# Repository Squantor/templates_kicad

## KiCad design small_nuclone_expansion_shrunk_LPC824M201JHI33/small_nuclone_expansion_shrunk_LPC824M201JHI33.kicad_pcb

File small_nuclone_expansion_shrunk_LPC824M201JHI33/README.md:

# LPC824M201JHI33 nuclone shrunk expansion board 
Template small nuclone expansion board for the [LPC824M201JHI33 nuclone](https://github.com/Squantor/squantorDevelBoards/tree/master/hardware/nuclone_LPC824M201JHI33/README.md).
# HSI (Hardware Software Interface)
This applies to a project that has a embedded software component. Describe what each pin/bus does, what it is connected to, what its function is and some "safe" behaviour when starting up.
## TODO's
Still some things need to be done:
* schematic entry 
* PCB layout
* Review with one night in between
* Produce at [OSHPARK](https://oshpark.com/)
* Assemble
* Test & characterise
* update Readme.md with pictures and BOM
## BOM

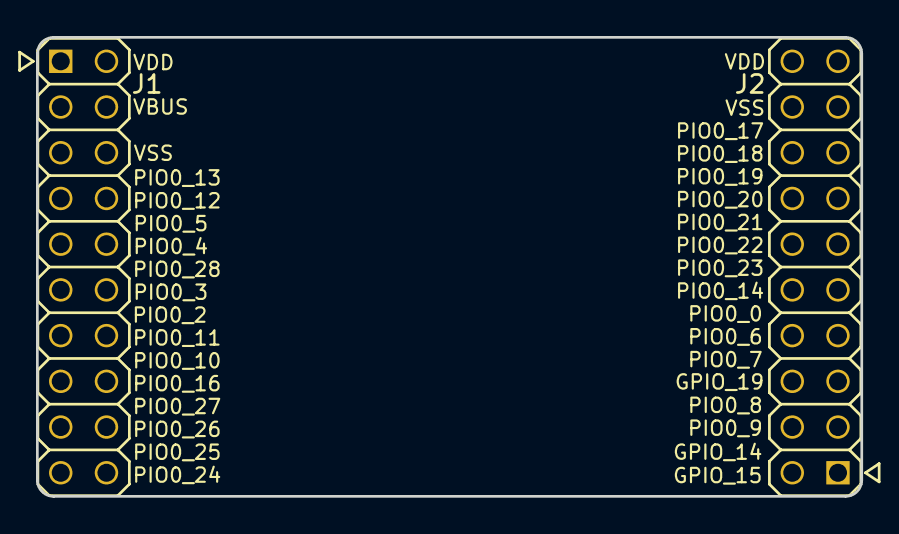
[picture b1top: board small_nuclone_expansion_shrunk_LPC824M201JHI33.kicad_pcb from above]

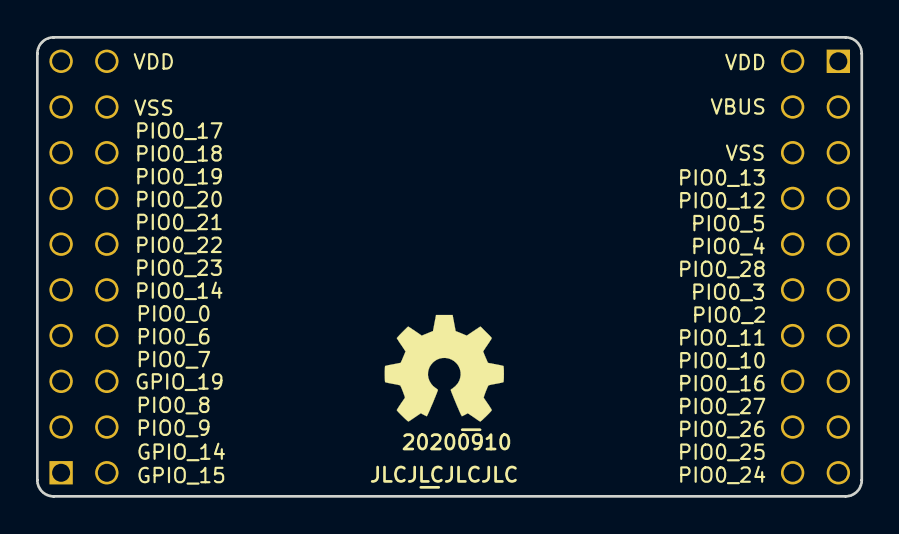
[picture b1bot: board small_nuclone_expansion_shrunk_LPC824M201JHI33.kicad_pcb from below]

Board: 2 copper layers, 45.8 x 25.5 mm, 5 parts (3 on the bottom side), 3 nets, no tracks yet.

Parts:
J1: nuclone_small_left; Header-0254-2X10-H010
J2: nuclone_small_right; Header-0254-2X10-H010
N1: OHWLOGO; OSHW-Symbol_6.7x6mm_SilkScreen
N2: 20200910; Label_Generic
N3: JLCJLCJLCJLC; Label_Generic

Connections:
/VBUS: J1.3, J1.4
/VDD: J1.1, J1.2, J2.19, J2.20
/VSS: J1.5, J1.6, J2.17, J2.18
